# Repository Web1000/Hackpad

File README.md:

# Toner's Media + Osu Macropad
Here's my submission for my macropad! I created a two-in-one macropad that doubles as a media player, allowing fast forward and rewind as well as volume and brightness adjustments using rotary encoders.

## PCB and Schematic
Here's a picture of my schematic!

Schematic            |  PCB
:-------------------------:|:-------------------------:
  |  

- [x] I ran DRC in KiCad and have made sure there are 0 errors!

## Assembled Render:
 |  

This was made in fusion 360

## BOM
* 2x Cherry MX Switches
* 2x SK6812 MINI-E LEDS
* 2x EC11 Rotary Encoders
* 1x Seeed XIAO RP2040
* 2x Blank DSA Keycaps (white)
* 4x M3x16 Screws
* 4x M3 Heatset Inserts
* KMK Firmware

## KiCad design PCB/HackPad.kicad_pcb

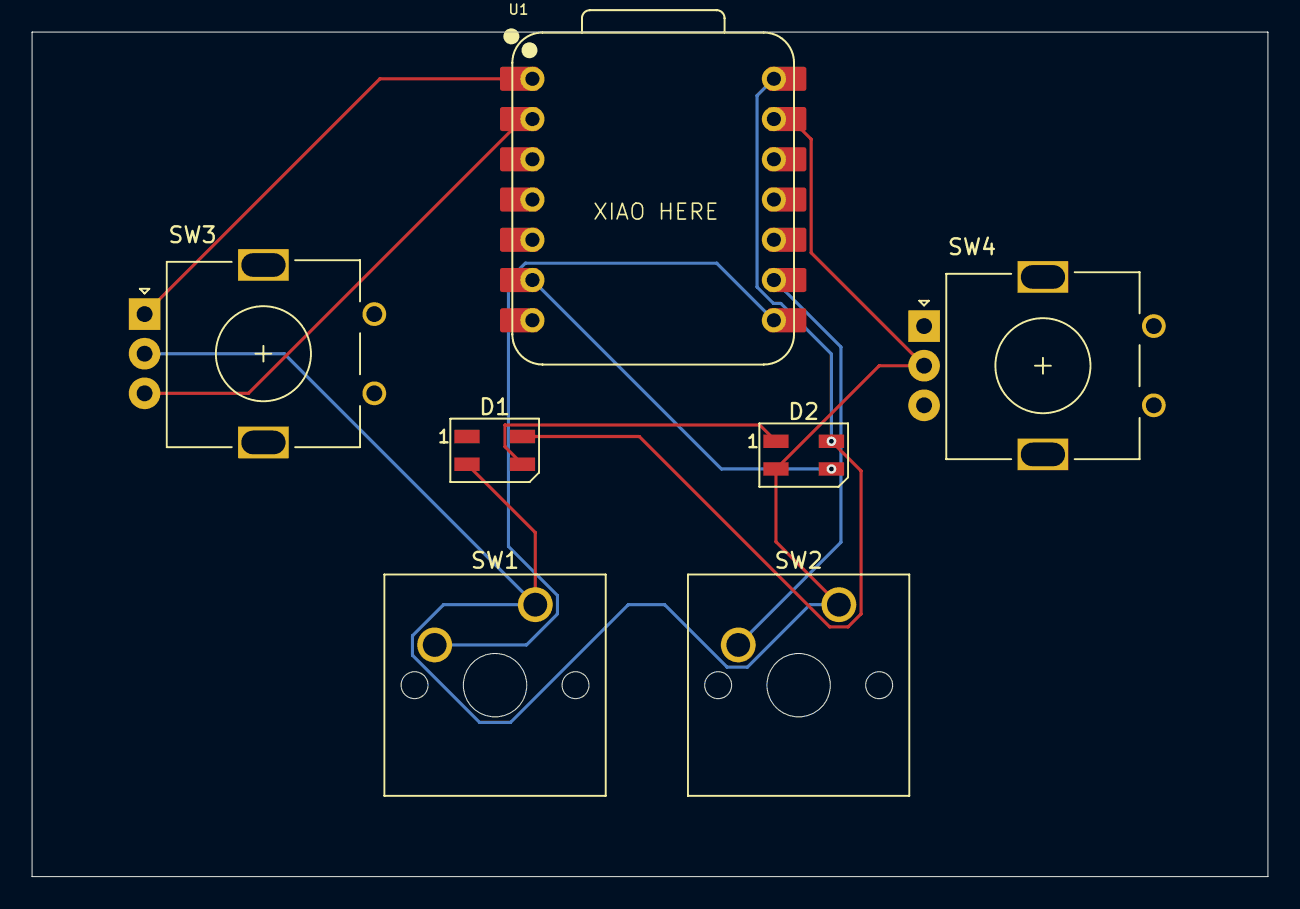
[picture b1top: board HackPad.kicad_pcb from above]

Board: 2 copper layers, 78.0 x 53.3 mm, 7 parts (0 on the bottom side), 8 nets.

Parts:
D1, D2: SK6812MINI; LED_SK6812MINI_PLCC4_3.5x3.5mm_P1.75mm
SW1, SW2: SW_Push; SW_Cherry_MX_1.00u_PCB
SW3, SW4: RotaryEncoder; RotaryEncoder_Alps_EC11E_Vertical_H20mm
U1: XIAO-RP2040-DIP

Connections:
+5V: D1.4 (VDD), D2.4 (VDD), U1.14 (VBUS)
GND: D1.2 (VSS), D2.2 (VSS), SW1.1, SW2.1, SW3.C, SW4.C, U1.13 (GND)
unnamed: D1.3 (DIN), D2.1 (DOUT)
unnamed: D2.3 (DIN), U1.6 (GPIO7/SCL)
unnamed: SW1.2, U1.8 (GPIO1/RX)
unnamed: SW2.2, U1.9 (GPIO2/SCK)
unnamed: SW3.A, U1.1 (GPIO26/ADC0/A0)
unnamed: SW3.B, U1.2 (GPIO27/ADC1/A1)

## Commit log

2026-01-02 Add README
2026-01-02 Final README
2026-01-02 Add images to root folder
2026-01-02 Add fit
2026-01-05 Updated Submission
2026-01-07 Changes made
2026-01-07 step files
2026-01-07 Added TOP
